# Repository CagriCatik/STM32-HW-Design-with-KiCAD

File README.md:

<div align="center">

<h2>STM32 Hardware Design with KiCad</h2>

</div>

A hands-on, end-to-end STM32 hardware project in KiCad 10: schematic, PCB layout, routing, manufacturing data,
firmware and documentation. It started as a course exercise (a minimal STM32F103 board) and grew into a complete,
manufacturable **controller for an RC car**.

The goal is not only to learn KiCad, but to understand what makes a microcontroller board electrically reliable,
layout-aware and production-ready, and to keep every step reproducible with scripts.

## The board (Rev C)

- STM32F103C8T6 at 72 MHz (8 MHz crystal), USB-C virtual COM port, Cortex-Debug connector
- 2S–3S LiPo input on XT30 with reverse protection, TPS563201 5 V / 3 A servo rail, AP2112K 3.3 V
- DRV8870 brushed motor driver (3.3 A limit), 4 servo/ESC outputs, 3 receiver inputs
- WS2812 RGB lighting output for 6 LEDs (front, sills, rear) with 5 V level shifter, 2 switched outputs
- LSM6DS3TR-C IMU, Qwiic, UART header, 2×5 expansion header
- 70 × 50 mm, 4 layers (solid GND plane), four M3 holes, JLCPCB assembly with an LCSC number on every part
- ERC 0/0, DRC 0 violations / 0 unconnected / 0 schematic-parity issues, checked in CI

Full description: [Project chapter of the documentation](webpage/docs/09_Project/01_Overview.md).

<details>
<summary><strong>Rev C – blocks and pin map</strong></summary>

Rev C turns the board into a complete controller for an RC car on one 70 × 50 mm, 4-layer PCB with four M3 holes.

| Block | Parts | MCU pins |
|---|---|---|
| Battery | 2S–3S LiPo on XT30, AO4407A reverse protection, SMAJ15A TVS, voltage sense 33k/10k | PA4 (ADC) |
| Servo rail | TPS563201 buck, 5.07 V / 3 A for servos and receiver | – |
| Logic supply | servo rail or USB-C (each via B5819W) → AP2112K-3.3 | – |
| Motor | DRV8870 brushed motor driver, 3.3 A current limit (0.1 Ω shunt), screw terminal | PA6/PA7 (TIM3 CH1/2) |
| Servo / ESC outputs | 4 × 3-pin (S, 5 V, GND) | PA0–PA3 (TIM2 CH1–4) |
| Receiver inputs | 3 × 3-pin, 1k series, powered from the servo rail | PB6–PB8 (TIM4 CH1–3, 5 V tolerant) |
| RGB lights | WS2812 chain, 6 LEDs, 74AHCT1G125 level shifter, 330 Ω | PA8 (TIM1 CH1 + DMA) |
| Switched outputs | 2 × AO3400A low-side outputs (5 V) | PB0/PB1 (TIM3 CH3/4) |
| IMU | LSM6DS3TR-C, I²C 0x6A, INT1/INT2 | PB10/PB11 (I2C2), PB12/PB13 |
| Other | USB-C, Cortex-Debug 10-pin, Qwiic, UART header, 2×5 expansion, user LED PC13 | |

Stack-up: F.Cu signals / In1 solid GND / In2 signals + GND fill / B.Cu signals + GND fill.
DRC: 0 violations, 0 unconnected, 0 schematic parity issues. Fabrication data: `stm32_prototype/production/rev-c/`.

Notes: the DRV8870 needs ≥ 6.5 V (it locks out on an empty 2S pack). When an ESC is plugged into a servo
output, disconnect its BEC red wire – the board already supplies 5 V.

```bash
python3 scripts/revc_schematic/gen.py <dir>   # schematic generator (+ check.sh)
scripts/route_revb.sh                         # autoroute (Freerouting) + GND pours + DRC
scripts/export_fab.sh                         # Gerber/drill/BOM/CPL/PDF/STEP for rev-c
```

</details>

## Repository layout

```text
stm32_prototype/          KiCad 10 project (schematic sheets, PCB, rules, project symbol library)
  production/rev-c/       Gerber ZIP, BOM, CPL, schematic PDF, renders, STEP
scripts/                  schematic generator, board setup, placement, routing, fabrication export
firmware/                 STM32CubeMX project (rc_controller) and the bring-up application
webpage/                  documentation site, built with Zensical (course + project chapter)
datasheets/               datasheets used during the design
.github/workflows/        hw-check.yml (ERC/DRC, fab data on tags), deploy.yml (docs)
```

## Quick start

```bash
# open the design
open stm32_prototype/stm32_prototype.kicad_pro            # KiCad 10

# checks (the same ones CI runs)
kicad-cli sch erc --severity-all --exit-code-violations stm32_prototype/stm32_prototype.kicad_sch
kicad-cli pcb drc --severity-all --exit-code-violations --schematic-parity stm32_prototype/stm32_prototype.kicad_pcb

# fabrication data for JLCPCB
scripts/export_fab.sh

# firmware (Arm GNU toolchain on PATH)
cd firmware/rc_controller && cmake -S . -B build -G "Unix Makefiles" \
  -DCMAKE_TOOLCHAIN_FILE=cmake/gcc-arm-none-eabi.cmake -DCMAKE_BUILD_TYPE=Release && cmake --build build

# documentation
pip install -r requirements.txt && cd webpage && zensical serve   # http://127.0.0.1:8000
```

Before ordering, check the part rotations in JLCPCB's assembly preview, then follow the
[bring-up checklist](webpage/docs/09_Project/06_Bring-up.md).

## Revisions

| Rev | Content | Where |
|---|---|---|
| A | Course schematic: STM32F103, crystal, decoupling; no layout | `main` history |
| B | Blue-Pill-compatible board: USB-C, ESD, AP2112K, Cortex-Debug, Qwiic, 76.2 × 22.86 mm | branch `rev-b-usb-c` |
| C | RC-car controller (this README) | branch `rev-c-rc-car` |

<details>
<summary><strong>Rev B – changes compared to Rev A</strong></summary>

Rev B is a modernised, Blue-Pill-compatible board (branch `rev-b-usb-c`); Rev C builds on it.

| Area | Rev A | Rev B |
|---|---|---|
| Schematic | single sheet, 15 of 16 parts without footprint | hierarchical sheets `mcu`, `power_usb`, `connectors`; footprint, LCSC and MPN on every part |
| USB | USB Micro | USB-C 2.0 device (5.1k CC resistors), USBLC6-2SC6 ESD, 500 mA PTC |
| Regulator | AMS1117-3.3 | AP2112K-3.3 (250 mV dropout, ceramic stable), Schottky against back-feeding |
| Clock | 16 MHz, 10 pF | 8 MHz (CubeMX default), 15 pF from C = 2·(C_L − C_stray); optional 32.768 kHz LSE (DNP) |
| Reset/boot | slide switch, R1 without value, BOOT1 floating | RESET + BOOT0 buttons, 10k pull-downs on BOOT0 and BOOT1, 100 nF on NRST (was 100 µF) |
| Analog supply | VDDA tied to 3V3 before the ferrite | VDDA on its own net behind FB1 with 10 nF + 1 µF |
| Debug / I²C | 1×4 SWD | Cortex-Debug 10-pin + 1×4 SWD, Qwiic (PB6/PB7) with cuttable 4.7k pull-ups |
| Board | – | 76.2 × 22.86 mm, Blue-Pill header pinout (0.6" rows), 4 layers SIG/GND/GND/SIG, JLCPCB rules |
| Output | – | Gerber/drill/BOM/CPL/PDF/STEP in `stm32_prototype/production/rev-b`, CI ERC + DRC |

Reproducible steps (KiCad 10 on macOS; paths in the scripts):

```bash
scripts/export_fab.sh                 # fabrication data via kicad-cli
scripts/route_revb.sh                 # re-route with Freerouting (needs Java 25 + freerouting 2.5)
```

</details>

## Course progress

<details>
<summary><strong>Checklist</strong></summary>

**1. Schematic design**

- [X] STM32 microcontroller fundamentals and decoupling guidance
- [X] STM32 configuration pin requirements and best practices
- [X] Pin-out management with STM32CubeMX (`firmware/rc_controller/rc_controller.ioc`)
- [X] Crystal oscillator circuit design
- [X] USB interface design for STM32 systems
- [X] Power supply design and connector selection
- [X] ERC, annotation workflow and validation
- [X] Component footprint assignment

**2. PCB layout**

- [X] KiCad PCB project setup and configuration
- [X] Placement of MCU, decoupling capacitors and crystal
- [X] USB and SWD interface layout
- [X] Footprints and 3D models
- [X] Connector and switch placement
- [X] Power distribution and grounding
- [X] Board outline and mounting holes

**3. PCB routing**

- [X] Decoupling and crystal routing
- [X] Signal routing
- [X] Power routing and current handling
- [X] Refinement and DRC

**4. Manufacturing**

- [X] BOM, Gerber, drill and pick-and-place files
- [ ] JLCPCB assembly preview checked
- [ ] Boards ordered and brought up

**5. Firmware**

- [X] CubeMX configuration and bring-up application (builds)
- [ ] Tested on hardware

</details>

## Resources

- Course this project started from: [Learn KiCad V6 and STM32 Hardware Design](https://www.udemy.com/course/learn-kicad-v6-and-stm32-hardware-design/) (KiCad 6; this repository uses KiCad 10)
- [KiCad documentation](https://docs.kicad.org/) and [kicad-cli reference](https://docs.kicad.org/master/en/cli/cli.html)
- [STM32CubeMX](https://www.st.com/en/development-tools/stm32cubemx.html), [STM32F103C8 datasheet](datasheets/datasheet_stm32f103c8.pdf)
- ST application notes: AN2867 (oscillator design), AN4879 (USB hardware and PCB guidelines)
- [JLCPCB capabilities](https://jlcpcb.com/capabilities/pcb-capabilities) and [parts library](https://jlcpcb.com/parts)

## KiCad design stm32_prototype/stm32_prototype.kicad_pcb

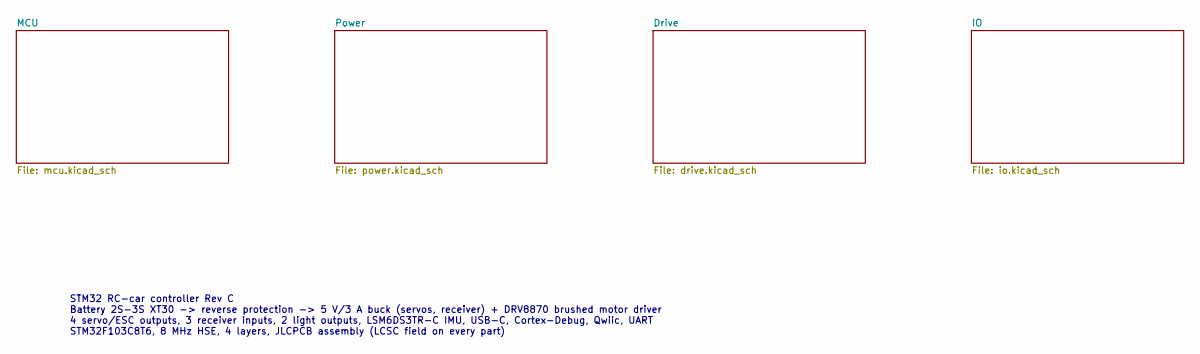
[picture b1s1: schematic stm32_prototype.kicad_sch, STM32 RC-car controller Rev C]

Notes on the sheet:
STM32 RC-car controller Rev C Battery 2S-3S XT30 -> reverse protection -> 5 V/3 A buck (servos, receiver) + DRV8870 brushed motor driver 4 servo/ESC outputs, 3 receiver inputs, 2 light outputs, LSM6DS3TR-C IMU, USB-C, Cortex-Debug, Qwiic, UART STM32F103C8T6, 8 MHz HSE, 4 layers, JLCPCB assembly (LC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

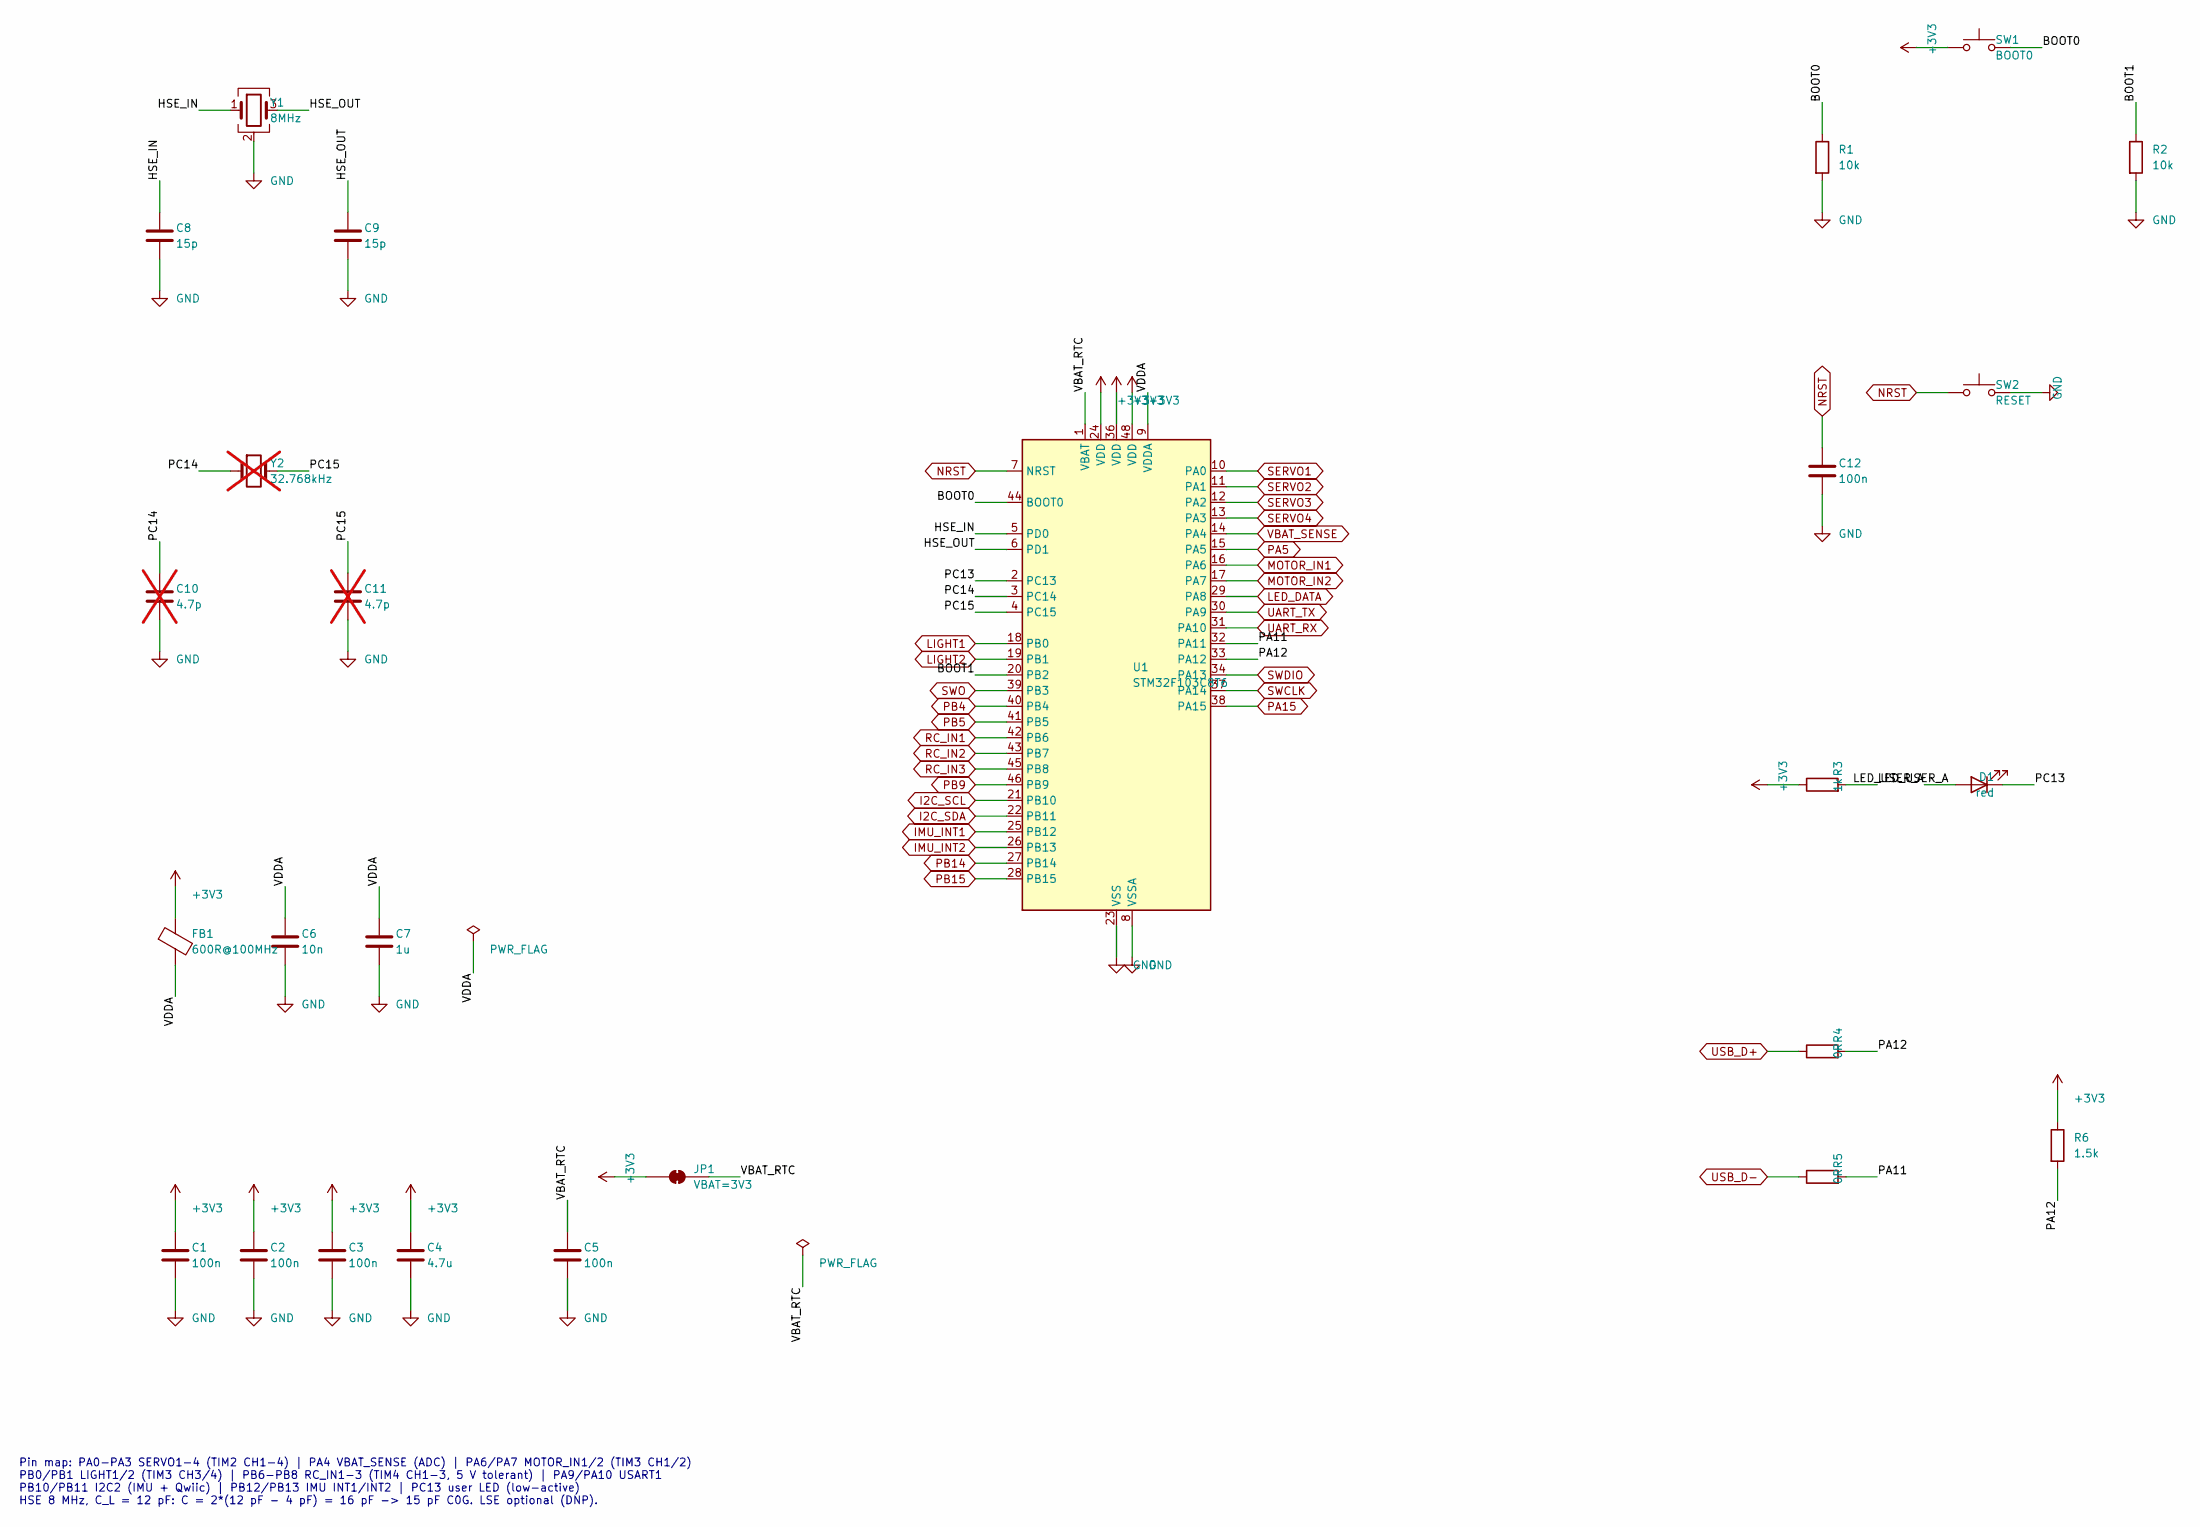
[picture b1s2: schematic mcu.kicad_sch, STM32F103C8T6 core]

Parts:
C1, C2, C3, C5, C12: 100n; C_0603_1608Metric; MPN CC0603KRX7R9BB104; LCSC C14663
C4: 4.7u; C_0603_1608Metric; MPN CL10A475KO8NNNC; LCSC C19666
C6: 10n; C_0603_1608Metric; MPN 0603B103K500NT; LCSC C57112
C7: 1u; C_0603_1608Metric; MPN CL10A105KB8NNNC; LCSC C15849
C8, C9: 15p; C_0603_1608Metric; MPN CL10C150JB8NNNC; LCSC C1644
C10, C11: 4.7p; C_0603_1608Metric; MPN 0603CG4R7C500NT; LCSC C1669; not fitted
D1: red; LED_0603_1608Metric; MPN KT-0603R; LCSC C2286
FB1: 600R@100MHz; L_0603_1608Metric; MPN GZ1608D601TF; LCSC C1002
JP1: VBAT=3V3; SolderJumper-2_P1.3mm_Bridged_RoundedPad1.0x1.5mm
R1, R2: 10k; R_0603_1608Metric; MPN 0603WAF1002T5E; LCSC C25804
R3: 1k; R_0603_1608Metric; MPN 0603WAF1001T5E; LCSC C21190
R4, R5: 0R; R_0603_1608Metric; MPN 0603WAF0000T5E; LCSC C21189
R6: 1.5k; R_0603_1608Metric; MPN 0603WAF1501T5E; LCSC C22843
SW1: BOOT0; SW_Push_1P1T_XKB_TS-1187A; MPN TS-1187A-B-A-B; LCSC C318884
SW2: RESET; SW_Push_1P1T_XKB_TS-1187A; MPN TS-1187A-B-A-B; LCSC C318884
U1: STM32F103C8T6; LQFP-48_7x7mm_P0.5mm; MPN STM32F103C8T6; LCSC C8734
Y1: 8MHz; Crystal_SMD_3225-4Pin_3.2x2.5mm; MPN X32258MOB4SI; LCSC C2682775
Y2: 32.768kHz; Crystal_SMD_3215-2Pin_3.2x1.5mm; MPN Q13FC13500049; LCSC C95361; not fitted

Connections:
+3V3: C1.1, C2.1, C3.1, C4.1, FB1.1, JP1.1 (A), R3.1, R6.1, SW1.1, U1.24 (VDD), U1.36 (VDD), U1.48 (VDD); also elsewhere on the board
/MCU/BOOT0: R1.1, SW1.2, U1.44 (BOOT0)
/MCU/BOOT1: R2.1, U1.20 (PB2)
/MCU/HSE_IN: C8.1, U1.5 (PD0), Y1.1
/MCU/HSE_OUT: C9.1, U1.6 (PD1), Y1.3
/MCU/LED_USER_A: D1.2 (A), R3.2
/MCU/PA11: R5.2, U1.32 (PA11)
/MCU/PA12: R4.2, R6.2, U1.33 (PA12)
/MCU/PC13: D1.1 (K), U1.2 (PC13)
/MCU/PC14: C10.1, U1.3 (PC14), Y2.1
/MCU/PC15: C11.1, U1.4 (PC15), Y2.2
/MCU/VBAT_RTC: C5.1, JP1.2 (B), U1.1 (VBAT)
/MCU/VDDA: C6.1, C7.1, FB1.2, U1.9 (VDDA)
GND: C1.2, C2.2, C3.2, C4.2, C5.2, C6.2, C7.2, C8.2, C9.2, C10.2, C11.2, C12.2, R1.2, R2.2, SW2.2, U1.8 (VSSA), U1.23 (VSS), U1.35 (VSS), U1.47 (VSS), Y1.2 (G), Y1.4 (G); also elsewhere on the board
I2C_SCL: U1.21 (PB10); also elsewhere on the board
I2C_SDA: U1.22 (PB11); also elsewhere on the board
IMU_INT1: U1.25 (PB12); also elsewhere on the board
IMU_INT2: U1.26 (PB13); also elsewhere on the board
LED_DATA: U1.29 (PA8); also elsewhere on the board
LIGHT1: U1.18 (PB0); also elsewhere on the board
LIGHT2: U1.19 (PB1); also elsewhere on the board
MOTOR_IN1: U1.16 (PA6); also elsewhere on the board
MOTOR_IN2: U1.17 (PA7); also elsewhere on the board
NRST: C12.1, SW2.1, U1.7 (NRST); also elsewhere on the board
PA5: U1.15 (PA5); also elsewhere on the board
PA15: U1.38 (PA15); also elsewhere on the board
PB4: U1.40 (PB4); also elsewhere on the board
PB5: U1.41 (PB5); also elsewhere on the board
PB9: U1.46 (PB9); also elsewhere on the board
PB14: U1.27 (PB14); also elsewhere on the board
PB15: U1.28 (PB15); also elsewhere on the board
RC_IN1: U1.42 (PB6); also elsewhere on the board
RC_IN2: U1.43 (PB7); also elsewhere on the board
RC_IN3: U1.45 (PB8); also elsewhere on the board
SERVO1: U1.10 (PA0); also elsewhere on the board
SERVO2: U1.11 (PA1); also elsewhere on the board
SERVO3: U1.12 (PA2); also elsewhere on the board
SERVO4: U1.13 (PA3); also elsewhere on the board
SWCLK: U1.37 (PA14); also elsewhere on the board
SWDIO: U1.34 (PA13); also elsewhere on the board
SWO: U1.39 (PB3); also elsewhere on the board
UART_RX: U1.31 (PA10); also elsewhere on the board
UART_TX: U1.30 (PA9); also elsewhere on the board
USB_D+: R4.1; also elsewhere on the board
USB_D-: R5.1; also elsewhere on the board
VBAT_SENSE: U1.14 (PA4); also elsewhere on the board

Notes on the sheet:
Pin map: PA0-PA3 SERVO1-4 (TIM2 CH1-4) | PA4 VBAT_SENSE (ADC) | PA6/PA7 MOTOR_IN1/2 (TIM3 CH1/2) PB0/PB1 LIGHT1/2 (TIM3 CH3/4) | PB6-PB8 RC_IN1-3 (TIM4 CH1-3, 5 V tolerant) | PA9/PA10 USART1 PB10/PB11 I2C2 (IMU + Qwiic) | PB12/PB13 IMU INT1/INT2 | PC13 user LED (low-active) HSE 8 MHz, C_L = 12 pF: 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

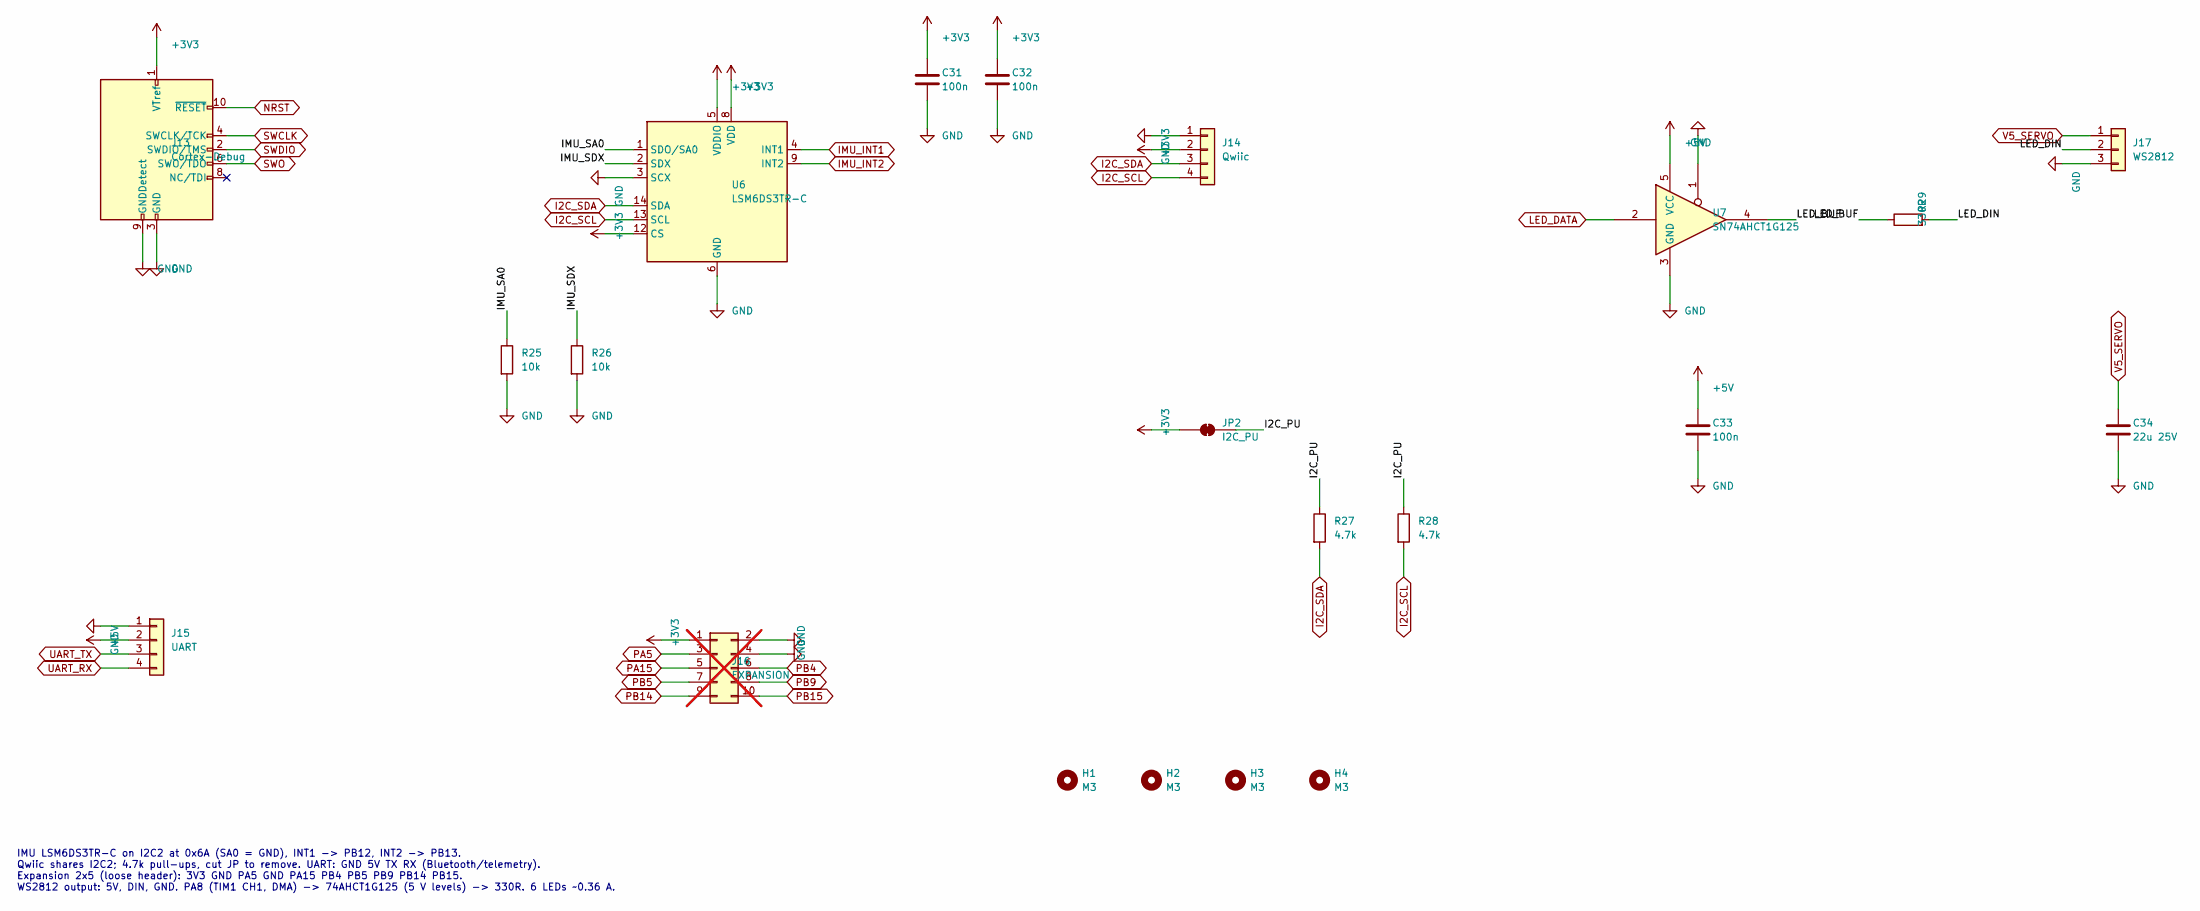
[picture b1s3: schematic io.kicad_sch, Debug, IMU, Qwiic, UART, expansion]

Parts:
C31, C32, C33: 100n; C_0603_1608Metric; MPN CC0603KRX7R9BB104; LCSC C14663
C34: 22u 25V; C_1206_3216Metric; MPN CL31A226KAHNNNE; LCSC C12891
H1, H2, H3, H4: M3; MountingHole_3.2mm_M3
J13: Cortex-Debug; PinHeader_2x05_P1.27mm_Vertical_SMD; MPN PZ127VS-12-10-H10-A38; LCSC C2935458
J14: Qwiic; JST_SH_SM04B-SRSS-TB_1x04-1MP_P1.00mm_Horizontal; MPN SM04B-SRSS-TB(LF)(SN); LCSC C160404
J15: UART; PinHeader_1x04_P2.54mm_Vertical; MPN PZ254V-11-04P; LCSC C2691448
J16: EXPANSION; PinHeader_2x05_P2.54mm_Vertical; MPN PZ254V-12-10P; LCSC C492422; not fitted
J17: WS2812; PinHeader_1x03_P2.54mm_Vertical; MPN 2.54-1*3P; LCSC C49257
JP2: I2C_PU; SolderJumper-2_P1.3mm_Bridged_RoundedPad1.0x1.5mm
R25, R26: 10k; R_0603_1608Metric; MPN 0603WAF1002T5E; LCSC C25804
R27, R28: 4.7k; R_0603_1608Metric; MPN 0603WAF4701T5E; LCSC C23162
R29: 330R; R_0603_1608Metric; MPN 0603WAF3300T5E; LCSC C23138
U6: LSM6DS3TR-C; LGA-14_3x2.5mm_P0.5mm_LayoutBorder3x4y; MPN LSM6DS3TR-C; LCSC C967633
U7: SN74AHCT1G125; SOT-23-5; MPN SN74AHCT1G125DBVR; LCSC C7484

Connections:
+3V3: C31.1, C32.1, J13.1 (VTref), J14.2, J16.1, JP2.1 (A), U6.5 (VDDIO), U6.8 (VDD), U6.12 (CS); also elsewhere on the board
+5V: C33.1, J15.2, U7.5 (VCC); also elsewhere on the board
/IO/I2C_PU: JP2.2 (B), R27.1, R28.1
/IO/IMU_SA0: R25.1, U6.1 (SDO/SA0)
/IO/IMU_SDX: R26.1, U6.2 (SDX)
/IO/LED_BUF: R29.1, U7.4
/IO/LED_DIN: J17.2, R29.2
GND: C31.2, C32.2, C33.2, C34.2, J13.3 (GND), J13.5 (GND), J13.9 (GNDDetect), J14.1, J15.1, J16.2, J16.4, J17.3, R25.2, R26.2, U6.3 (SCX), U6.6 (GND), U6.7 (GND), U7.1, U7.3 (GND); also elsewhere on the board
I2C_SCL: J14.4, R28.2, U6.13 (SCL); also elsewhere on the board
I2C_SDA: J14.3, R27.2, U6.14 (SDA); also elsewhere on the board
IMU_INT1: U6.4 (INT1); also elsewhere on the board
IMU_INT2: U6.9 (INT2); also elsewhere on the board
LED_DATA: U7.2; also elsewhere on the board
NRST: J13.10 (~RESET); also elsewhere on the board
PA5: J16.3; also elsewhere on the board
PA15: J16.5; also elsewhere on the board
PB4: J16.6; also elsewhere on the board
PB5: J16.7; also elsewhere on the board
PB9: J16.8; also elsewhere on the board
PB14: J16.9; also elsewhere on the board
PB15: J16.10; also elsewhere on the board
SWCLK: J13.4 (SWCLK/TCK); also elsewhere on the board
SWDIO: J13.2 (SWDIO/TMS); also elsewhere on the board
SWO: J13.6 (SWO/TDO); also elsewhere on the board
UART_RX: J15.4; also elsewhere on the board
UART_TX: J15.3; also elsewhere on the board
V5_SERVO: C34.1, J17.1; also elsewhere on the board

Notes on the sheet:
IMU LSM6DS3TR-C on I2C2 at 0x6A (SA0 = GND), INT1 -> PB12, INT2 -> PB13. Qwiic shares I2C2; 4.7k pull-ups, cut JP to remove. UART: GND 5V TX RX (Bluetooth/telemetry). Expansion 2x5 (loose header): 3V3 GND PA5 GND PA15 PB4 PB5 PB9 PB14 PB15. WS2812 output: 5V, DIN, GND. PA8 (TIM1 CH1, DMA) -> 74AHCT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

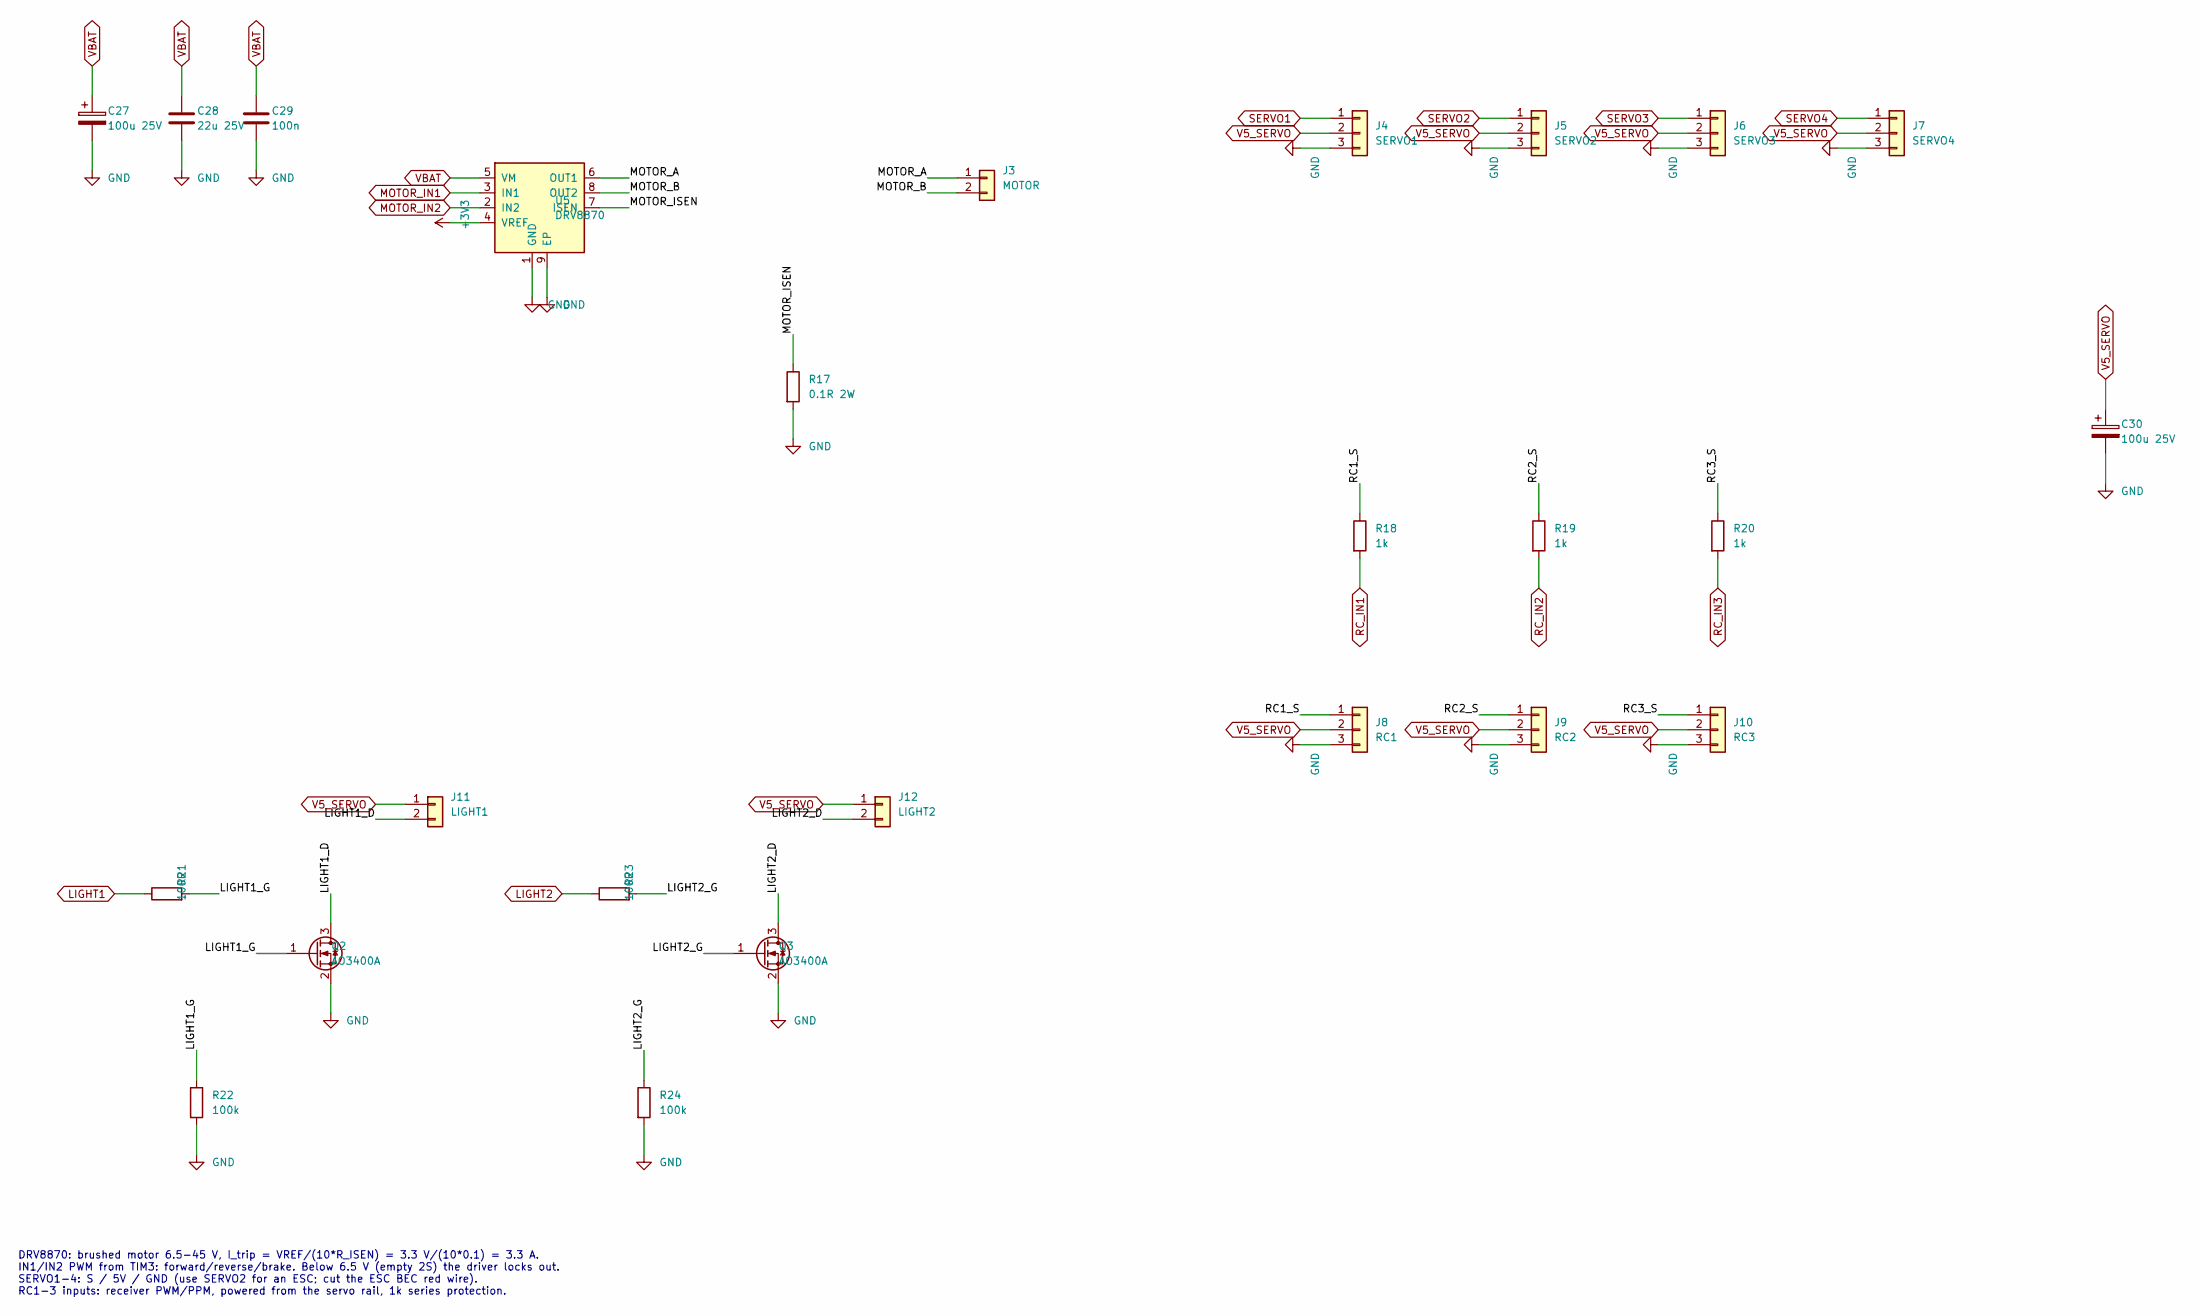
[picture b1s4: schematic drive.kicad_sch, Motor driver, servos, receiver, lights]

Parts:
C27, C30: 100u 25V; CP_Elec_6.3x7.7; MPN RVT1E101M0607; LCSC C72477
C28: 22u 25V; C_1206_3216Metric; MPN CL31A226KAHNNNE; LCSC C12891
C29: 100n; C_0603_1608Metric; MPN CC0603KRX7R9BB104; LCSC C14663
J3: MOTOR; TerminalBlock_Phoenix_PT-1,5-2-3.5-H_1x02_P3.50mm_Horizontal; MPN KF350-3.5-2P; LCSC C474892
J4: SERVO1; PinHeader_1x03_P2.54mm_Vertical; MPN 2.54-1*3P; LCSC C49257
J5: SERVO2; PinHeader_1x03_P2.54mm_Vertical; MPN 2.54-1*3P; LCSC C49257
J6: SERVO3; PinHeader_1x03_P2.54mm_Vertical; MPN 2.54-1*3P; LCSC C49257
J7: SERVO4; PinHeader_1x03_P2.54mm_Vertical; MPN 2.54-1*3P; LCSC C49257
J8: RC1; PinHeader_1x03_P2.54mm_Vertical; MPN 2.54-1*3P; LCSC C49257
J9: RC2; PinHeader_1x03_P2.54mm_Vertical; MPN 2.54-1*3P; LCSC C49257
J10: RC3; PinHeader_1x03_P2.54mm_Vertical; MPN 2.54-1*3P; LCSC C49257
J11: LIGHT1; PinHeader_1x02_P2.54mm_Vertical; MPN PZ254V-11-02P; LCSC C492401
J12: LIGHT2; PinHeader_1x02_P2.54mm_Vertical; MPN PZ254V-11-02P; LCSC C492401
Q2, Q3: AO3400A; SOT-23; MPN AO3400A; LCSC C20917
R17: 0.1R 2W; R_2512_6332Metric; MPN RLP25FEER100; LCSC C160587
R18, R19, R20: 1k; R_0603_1608Metric; MPN 0603WAF1001T5E; LCSC C21190
R21, R23: 100R; R_0603_1608Metric; MPN 0603WAF1000T5E; LCSC C22775
R22, R24: 100k; R_0603_1608Metric; MPN 0603WAF1003T5E; LCSC C25803
U5: DRV8870; Texas_HSOP-8-1EP_3.9x4.9mm_P1.27mm_ThermalVias; MPN DRV8870DDAR; LCSC C86590

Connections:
+3V3: U5.4 (VREF); also elsewhere on the board
/Drive/LIGHT1_D: J11.2, Q2.3 (D)
/Drive/LIGHT1_G: Q2.1 (G), R21.2, R22.1
/Drive/LIGHT2_D: J12.2, Q3.3 (D)
/Drive/LIGHT2_G: Q3.1 (G), R23.2, R24.1
/Drive/MOTOR_A: J3.1, U5.6 (OUT1)
/Drive/MOTOR_B: J3.2, U5.8 (OUT2)
/Drive/MOTOR_ISEN: R17.1, U5.7 (ISEN)
/Drive/RC1_S: J8.1, R18.1
/Drive/RC2_S: J9.1, R19.1
/Drive/RC3_S: J10.1, R20.1
GND: C27.2, C28.2, C29.2, C30.2, J4.3, J5.3, J6.3, J7.3, J8.3, J9.3, J10.3, Q2.2 (S), Q3.2 (S), R17.2, R22.2, R24.2, U5.1 (GND), U5.9 (EP); also elsewhere on the board
LIGHT1: R21.1; also elsewhere on the board
LIGHT2: R23.1; also elsewhere on the board
MOTOR_IN1: U5.3 (IN1); also elsewhere on the board
MOTOR_IN2: U5.2 (IN2); also elsewhere on the board
RC_IN1: R18.2; also elsewhere on the board
RC_IN2: R19.2; also elsewhere on the board
RC_IN3: R20.2; also elsewhere on the board
SERVO1: J4.1; also elsewhere on the board
SERVO2: J5.1; also elsewhere on the board
SERVO3: J6.1; also elsewhere on the board
SERVO4: J7.1; also elsewhere on the board
V5_SERVO: C30.1, J4.2, J5.2, J6.2, J7.2, J8.2, J9.2, J10.2, J11.1, J12.1; also elsewhere on the board
VBAT: C27.1, C28.1, C29.1, U5.5 (VM); also elsewhere on the board

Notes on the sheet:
DRV8870: brushed motor 6.5-45 V, I_trip = VREF/(10*R_ISEN) = 3.3 V/(10*0.1) = 3.3 A. IN1/IN2 PWM from TIM3: forward/reverse/brake. Below 6.5 V (empty 2S) the driver locks out. SERVO1-4: S / 5V / GND (use SERVO2 for an ESC; cut the ESC BEC red wire). RC1-3 inputs: receiver PWM/PPM, powered from the 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

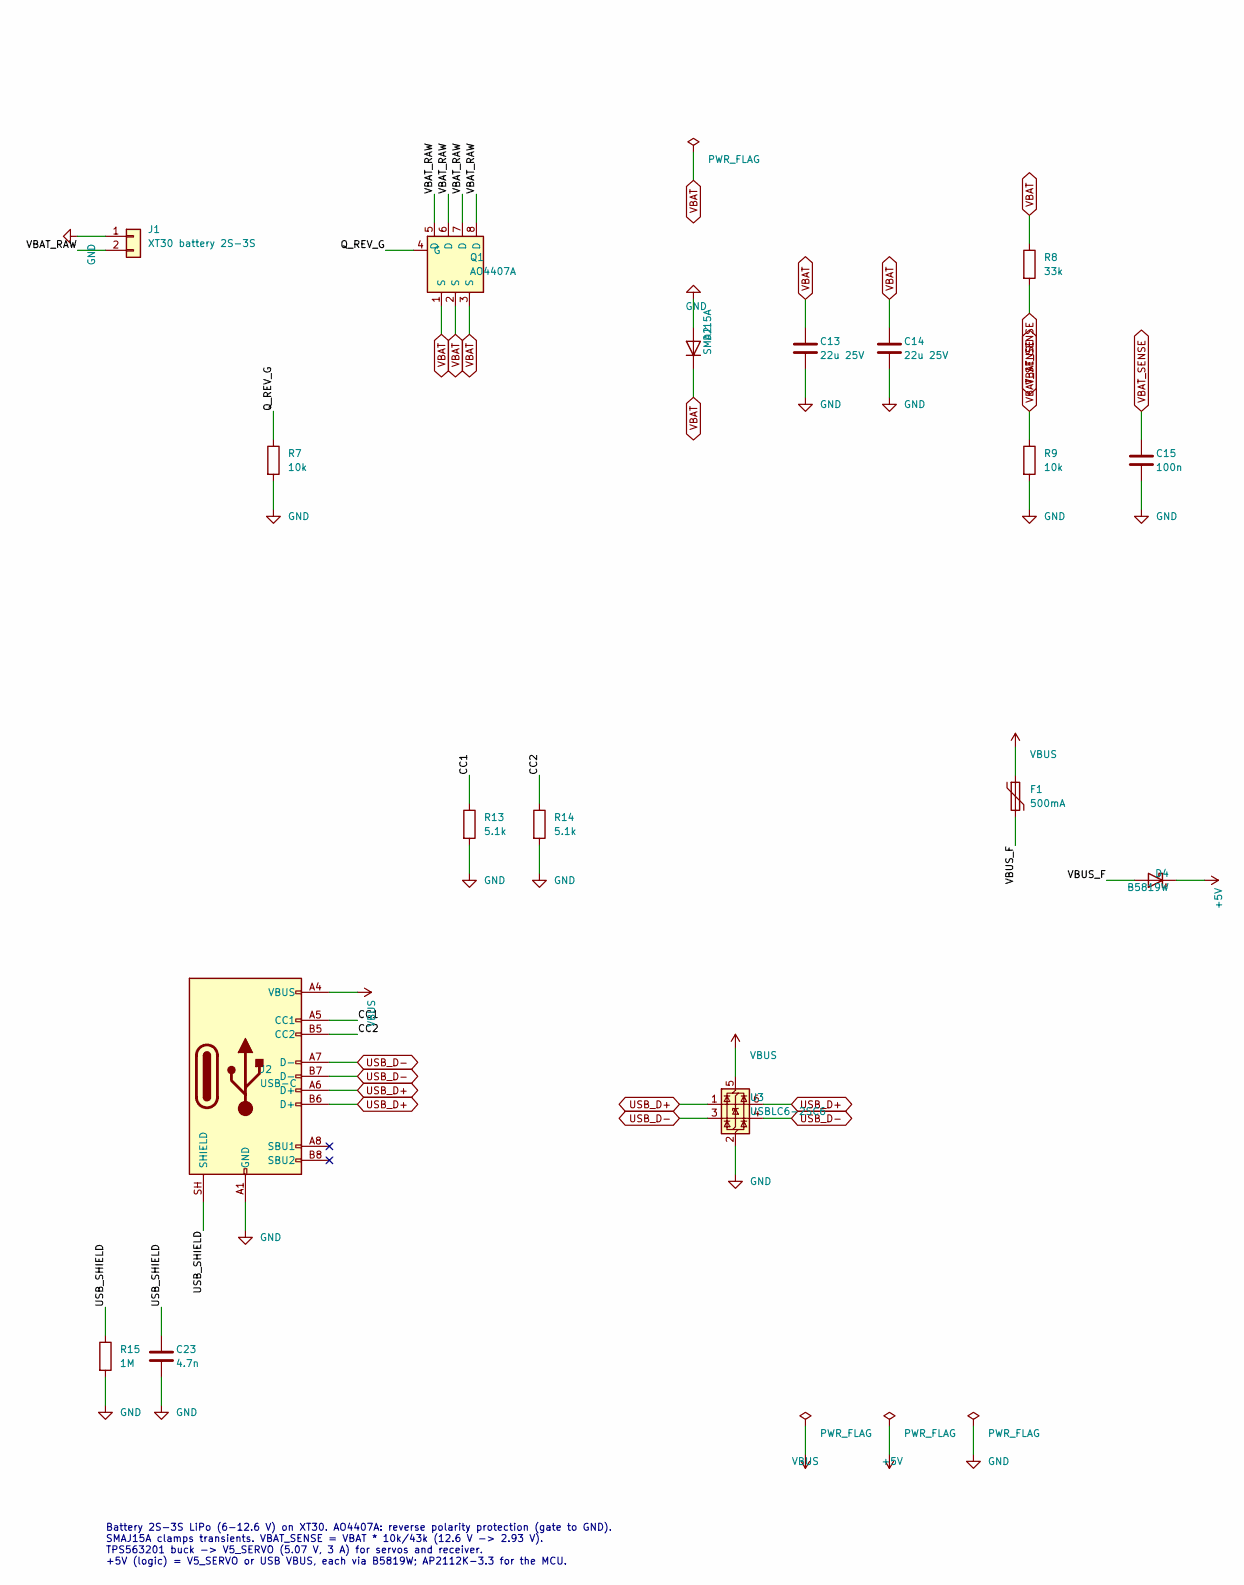
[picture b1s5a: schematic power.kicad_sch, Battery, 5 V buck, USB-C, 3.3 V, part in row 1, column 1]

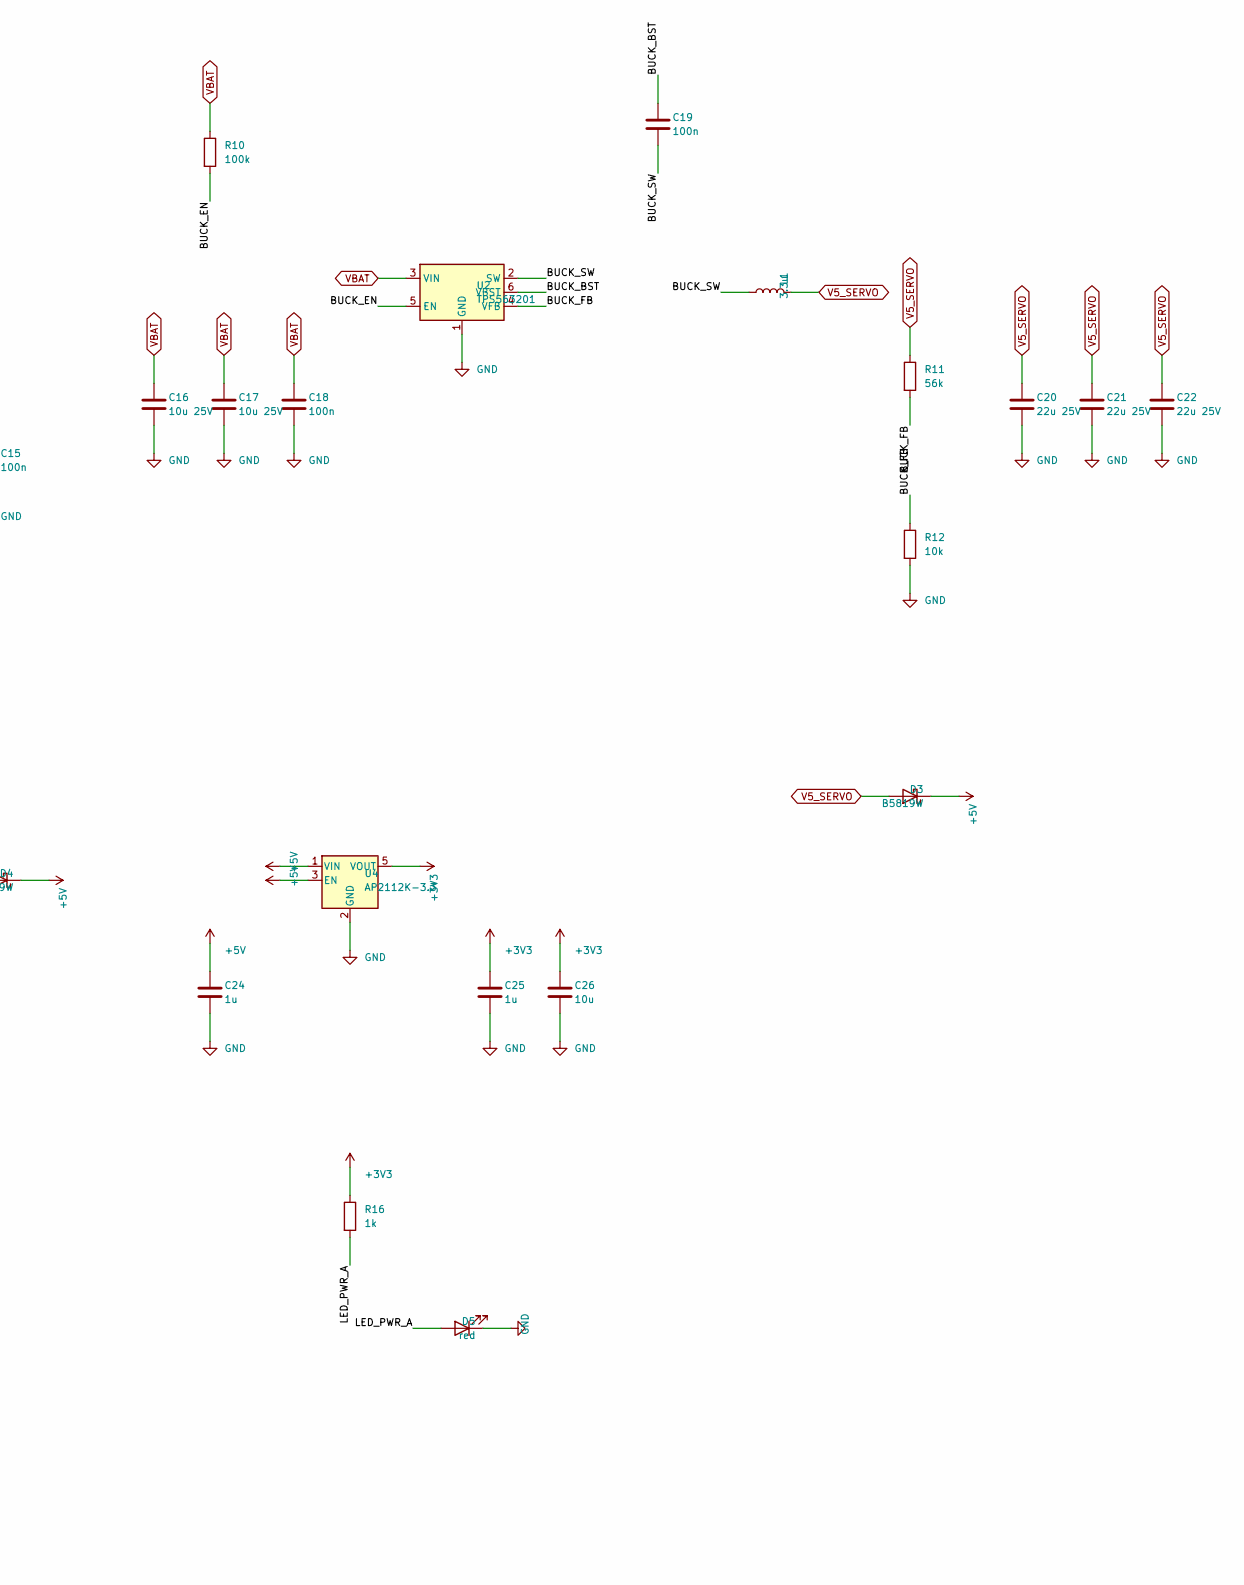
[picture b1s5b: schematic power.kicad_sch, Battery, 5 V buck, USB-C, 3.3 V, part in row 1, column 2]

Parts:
C13, C14: 22u 25V; C_1206_3216Metric; MPN CL31A226KAHNNNE; LCSC C12891
C15, C18, C19: 100n; C_0603_1608Metric; MPN CC0603KRX7R9BB104; LCSC C14663
C16, C17: 10u 25V; C_0805_2012Metric; MPN CL21A106KAYNNNE; LCSC C15850
C20, C21, C22: 22u 25V; C_0805_2012Metric; MPN CL21A226MAQNNNE; LCSC C45783
C23: 4.7n; C_0603_1608Metric; MPN 0603B472K500NT; LCSC C53987
C24, C25: 1u; C_0603_1608Metric; MPN CL10A105KB8NNNC; LCSC C15849
C26: 10u; C_0603_1608Metric; MPN CL10A106KP8NNNC; LCSC C19702
D2: SMAJ15A; D_SMA; MPN SMAJ15A; LCSC C353478
D3, D4: B5819W; D_SOD-123; MPN B5819W SL; LCSC C8598
D5: red; LED_0603_1608Metric; MPN KT-0603R; LCSC C2286
F1: 500mA; Fuse_1206_3216Metric; MPN nSMD050-33V; LCSC C70077
J1: XT30 battery 2S-3S; AMASS_XT30UPB-M_1x02_P5.0mm_Vertical; MPN XT30UPB-M; LCSC C428721
J2: USB-C; USB_C_Receptacle_HRO_TYPE-C-31-M-12; MPN TYPE-C-31-M-12; LCSC C165948
L1: 3.3u; L_Sunlord_SWPA6045S; MPN SWPA6045S3R3MT; LCSC C83456
Q1: AO4407A; SOIC-8_3.9x4.9mm_P1.27mm; MPN AO4407A; LCSC C16072
R7, R9, R12: 10k; R_0603_1608Metric; MPN 0603WAF1002T5E; LCSC C25804
R8: 33k; R_0603_1608Metric; MPN 0603WAF3302T5E; LCSC C4216
R10: 100k; R_0603_1608Metric; MPN 0603WAF1003T5E; LCSC C25803
R11: 56k; R_0603_1608Metric; MPN 0603WAF5602T5E; LCSC C23206
R13, R14: 5.1k; R_0603_1608Metric; MPN 0603WAF5101T5E; LCSC C23186
R15: 1M; R_0603_1608Metric; MPN 0603WAF1004T5E; LCSC C22935
R16: 1k; R_0603_1608Metric; MPN 0603WAF1001T5E; LCSC C21190
U2: TPS563201; TSOT-23-6; MPN TPS563201DDCR; LCSC C116592
U3: USBLC6-2SC6; SOT-23-6; MPN USBLC6-2SC6; LCSC C7519
U4: AP2112K-3.3; SOT-23-5; MPN AP2112K-3.3TRG1; LCSC C51118

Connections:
+3V3: C25.1, C26.1, R16.1, U4.5 (VOUT); also elsewhere on the board
+5V: C24.1, D3.1 (K), D4.1 (K), U4.1 (VIN), U4.3 (EN); also elsewhere on the board
/Power/BUCK_BST: C19.1, U2.6 (VBST)
/Power/BUCK_EN: R10.2, U2.5 (EN)
/Power/BUCK_FB: R11.2, R12.1, U2.4 (VFB)
/Power/BUCK_SW: C19.2, L1.1, U2.2 (SW)
/Power/CC1: J2.A5 (CC1), R13.1
/Power/CC2: J2.B5 (CC2), R14.1
/Power/LED_PWR_A: D5.2 (A), R16.2
/Power/Q_REV_G: Q1.4 (G), R7.1
/Power/USB_SHIELD: C23.1, J2.SH (SHIELD), R15.1
/Power/VBAT_RAW: J1.2, Q1.5 (D), Q1.6 (D), Q1.7 (D), Q1.8 (D)
/Power/VBUS_F: D4.2 (A), F1.2
GND: C13.2, C14.2, C15.2, C16.2, C17.2, C18.2, C20.2, C21.2, C22.2, C23.2, C24.2, C25.2, C26.2, D2.2 (A), D5.1 (K), J1.1, J2.A1 (GND), J2.A12 (GND), J2.B1 (GND), J2.B12 (GND), R7.2, R9.2, R12.2, R13.2, R14.2, R15.2, U2.1 (GND), U3.2 (GND), U4.2 (GND); also elsewhere on the board
USB_D+: J2.A6 (D+), J2.B6 (D+), U3.1 (I/O1), U3.6 (I/O1); also elsewhere on the board
USB_D-: J2.A7 (D-), J2.B7 (D-), U3.3 (I/O2), U3.4 (I/O2); also elsewhere on the board
V5_SERVO: C20.1, C21.1, C22.1, D3.2 (A), L1.2, R11.1; also elsewhere on the board
VBAT: C13.1, C14.1, C16.1, C17.1, C18.1, D2.1 (K), Q1.1 (S), Q1.2 (S), Q1.3 (S), R8.1, R10.1, U2.3 (VIN); also elsewhere on the board
VBAT_SENSE: C15.1, R8.2, R9.1; also elsewhere on the board
VBUS: F1.1, J2.A4 (VBUS), J2.A9 (VBUS), J2.B4 (VBUS), J2.B9 (VBUS), U3.5 (VBUS)

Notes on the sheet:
Battery 2S-3S LiPo (6-12.6 V) on XT30. AO4407A: reverse polarity protection (gate to GND). SMAJ15A clamps transients. VBAT_SENSE = VBAT * 10k/43k (12.6 V -> 2.93 V). TPS563201 buck -> V5_SERVO (5.07 V, 3 A) for servos and receiver. +5V (logic) = V5_SERVO or USB VBUS, each via B5819W; AP2112K-3.3 fo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
